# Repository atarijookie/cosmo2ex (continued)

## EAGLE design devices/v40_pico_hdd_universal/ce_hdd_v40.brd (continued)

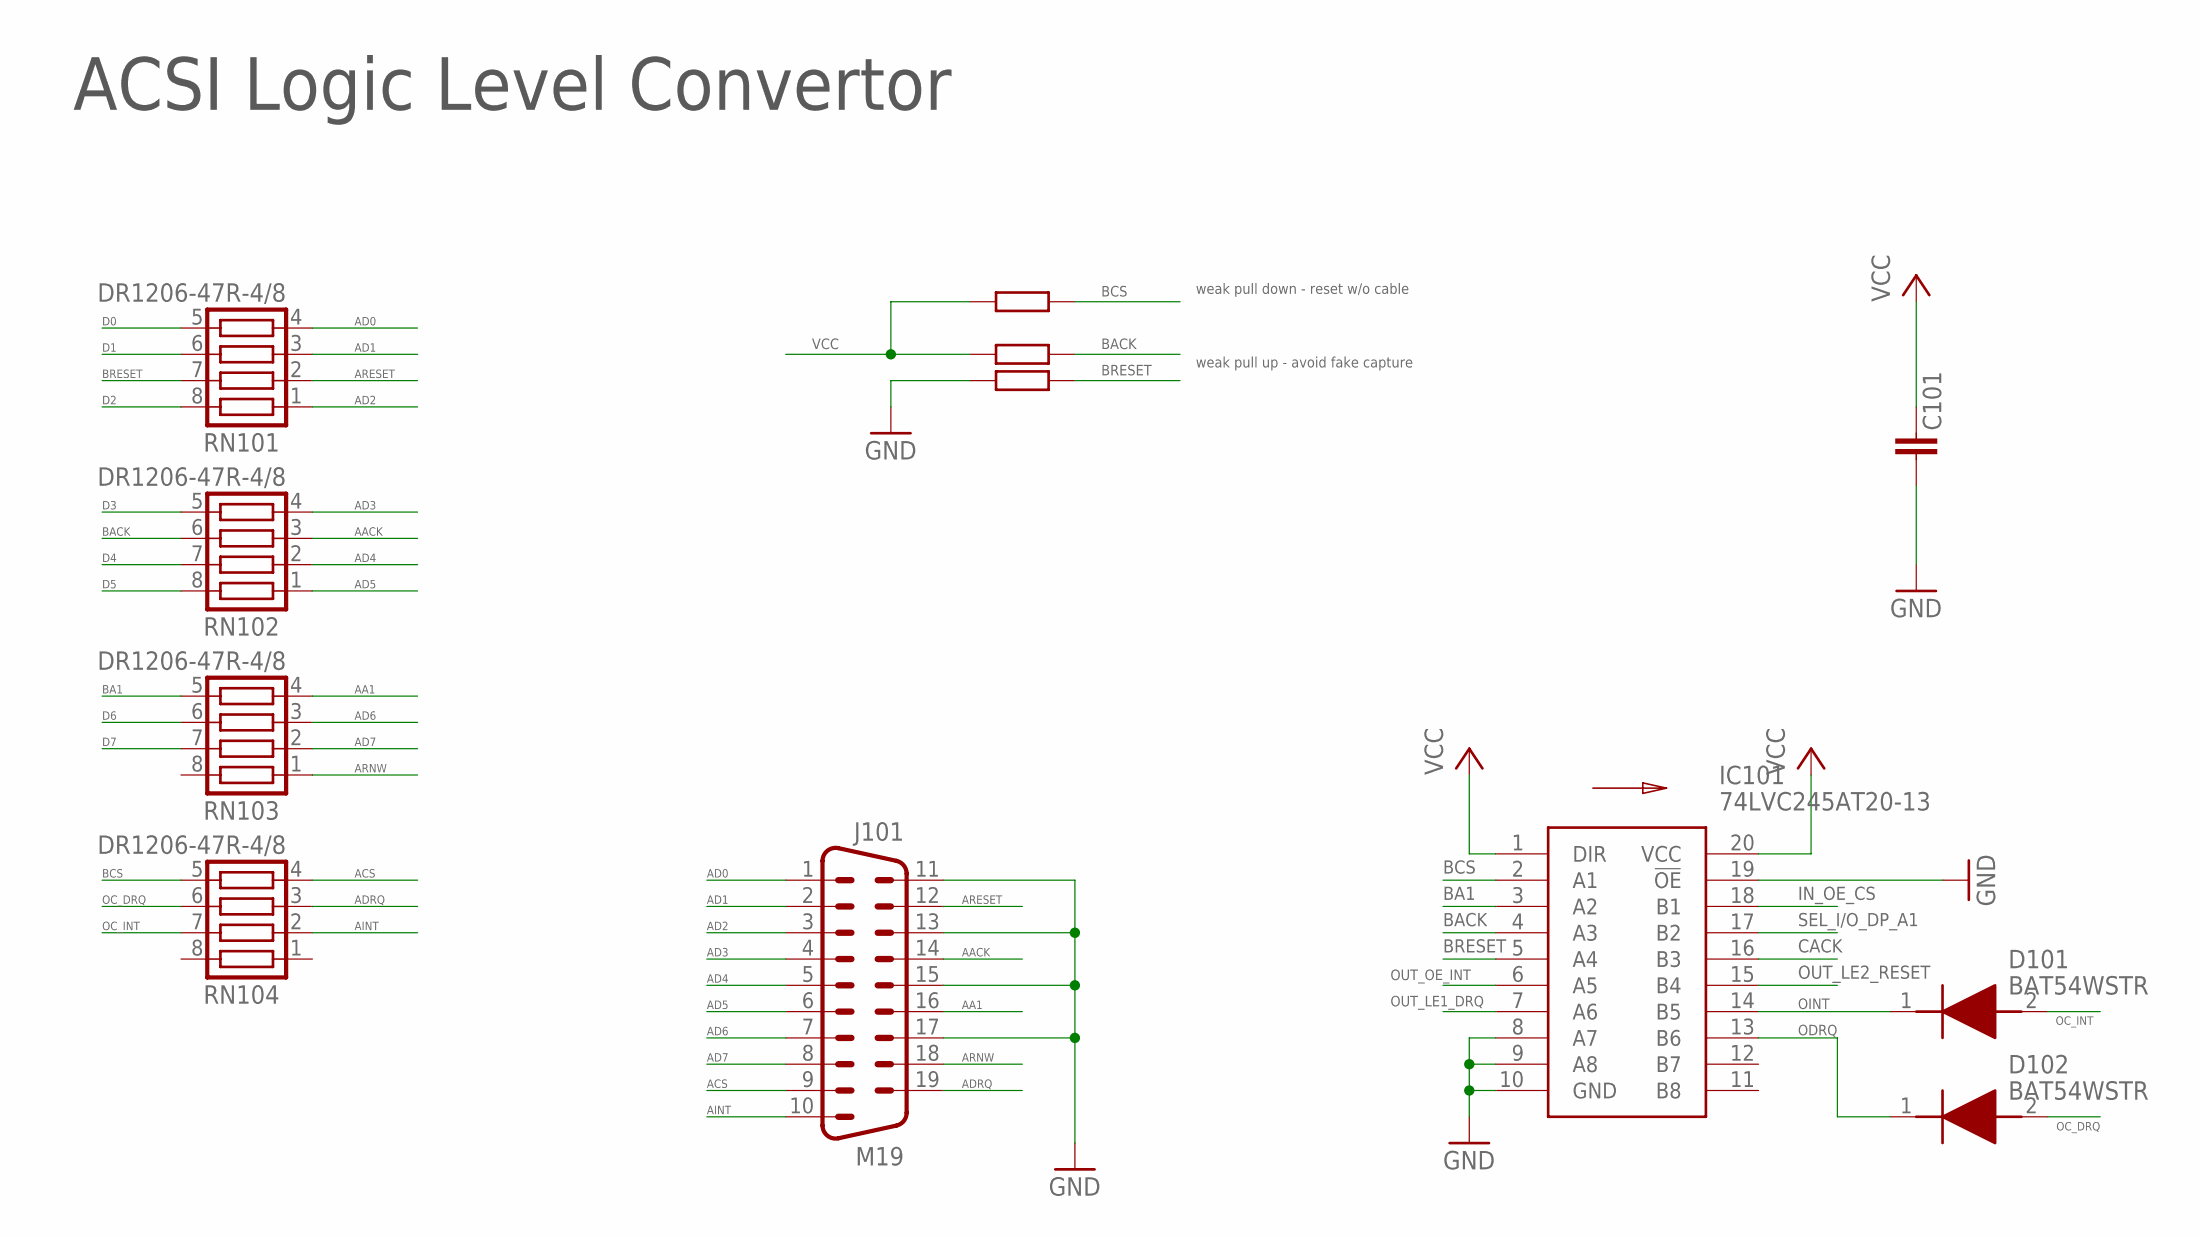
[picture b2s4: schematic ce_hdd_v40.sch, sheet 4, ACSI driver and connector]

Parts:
C101: 1 uF; C0603
D101: BAT54WSTR; SOD2613X100N
D102: BAT54WSTR; SOD2613X100N; MANUFACTURER_PART_NUMBER BAT54WSTR
IC101: 74LVC245AT20-13; SOP65P640X120-20N
J101: M19
R102, R103, R104: 10k; R0603
RN101, RN102, RN103, RN104: DR1206-47R-4/8; CTS742C083

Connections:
AA1: J101.16, RN103.4
AACK: J101.14, RN102.3
ACS: J101.9, RN104.4
AD0: J101.1, RN101.4
AD1: J101.2, RN101.3
AD2: J101.3, RN101.1
AD3: J101.4, RN102.4
AD4: J101.5, RN102.2
AD5: J101.6, RN102.1
AD6: J101.7, RN103.3
AD7: J101.8, RN103.2
ADRQ: J101.19, RN104.3
AINT: J101.10, RN104.2
ARESET: J101.12, RN101.2
ARNW: J101.18, RN103.1
BA1: IC101.3 (A2), RN103.5
BACK: IC101.4 (A3), R103.2, RN102.6
BCS: IC101.2 (A1), R102.2, RN104.5
BRESET: IC101.5 (A4), R104.2, RN101.7
CACK: IC101.16 (B3); also elsewhere on the board
D0: RN101.5; also elsewhere on the board
D1: RN101.6; also elsewhere on the board
D2: RN101.8; also elsewhere on the board
D3: RN102.5; also elsewhere on the board
D4: RN102.7; also elsewhere on the board
D5: RN102.8; also elsewhere on the board
D6: RN103.6; also elsewhere on the board
D7: RN103.7; also elsewhere on the board
GND: C101.2, IC101.8 (A7), IC101.9 (A8), IC101.10 (GND), IC101.19 (!OE), J101.11, J101.13, J101.15, J101.17, R104.1; also elsewhere on the board
IN_OE_CS: IC101.18 (B1); also elsewhere on the board
OC_DRQ: D102.2 (A), RN104.6
OC_INT: D101.2 (A), RN104.7
ODRQ: D102.1 (K), IC101.13 (B6)
OINT: D101.1 (K), IC101.14 (B5)
OUT_LE1_DRQ: IC101.7 (A6); also elsewhere on the board
OUT_LE2_RESET: IC101.15 (B4); also elsewhere on the board
OUT_OE_INT: IC101.6 (A5); also elsewhere on the board
SEL_I/O_DP_A1: IC101.17 (B2); also elsewhere on the board
VCC: C101.1, IC101.1 (DIR), IC101.20 (VCC), R102.1, R103.1; also elsewhere on the board

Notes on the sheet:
ACSI Logic Level Convertor
weak pull down - reset w/o cable
weak pull up - avoid fake capture

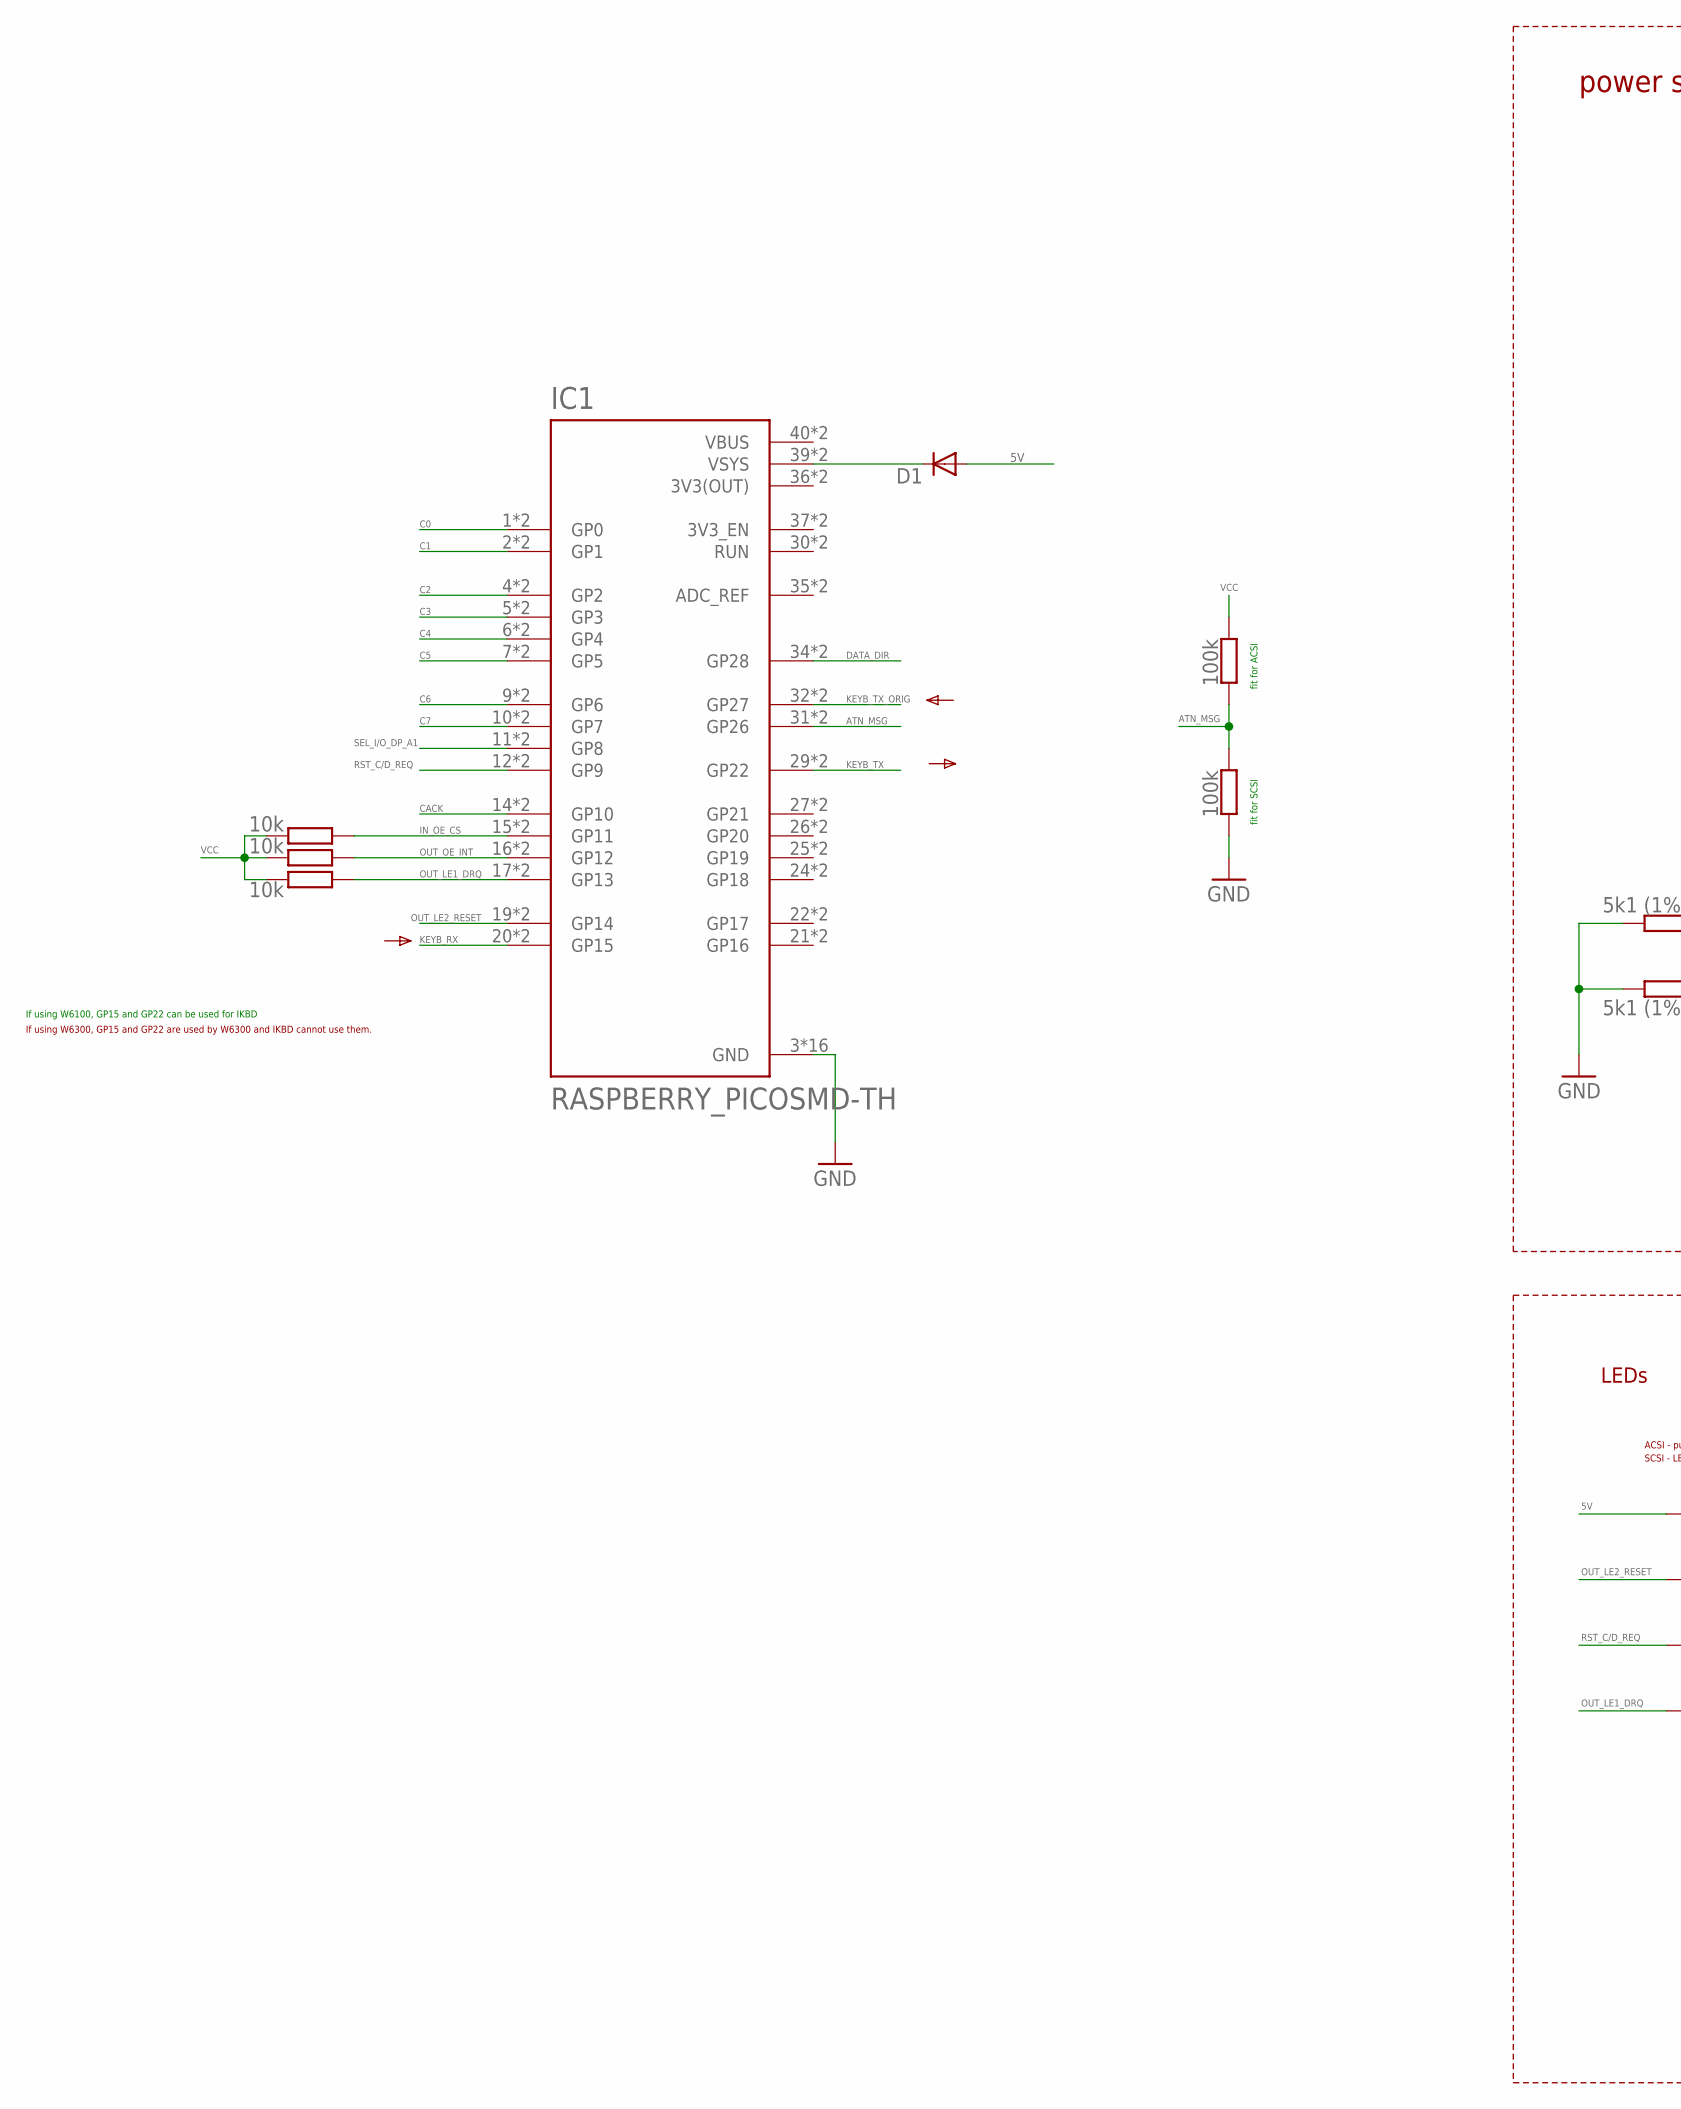
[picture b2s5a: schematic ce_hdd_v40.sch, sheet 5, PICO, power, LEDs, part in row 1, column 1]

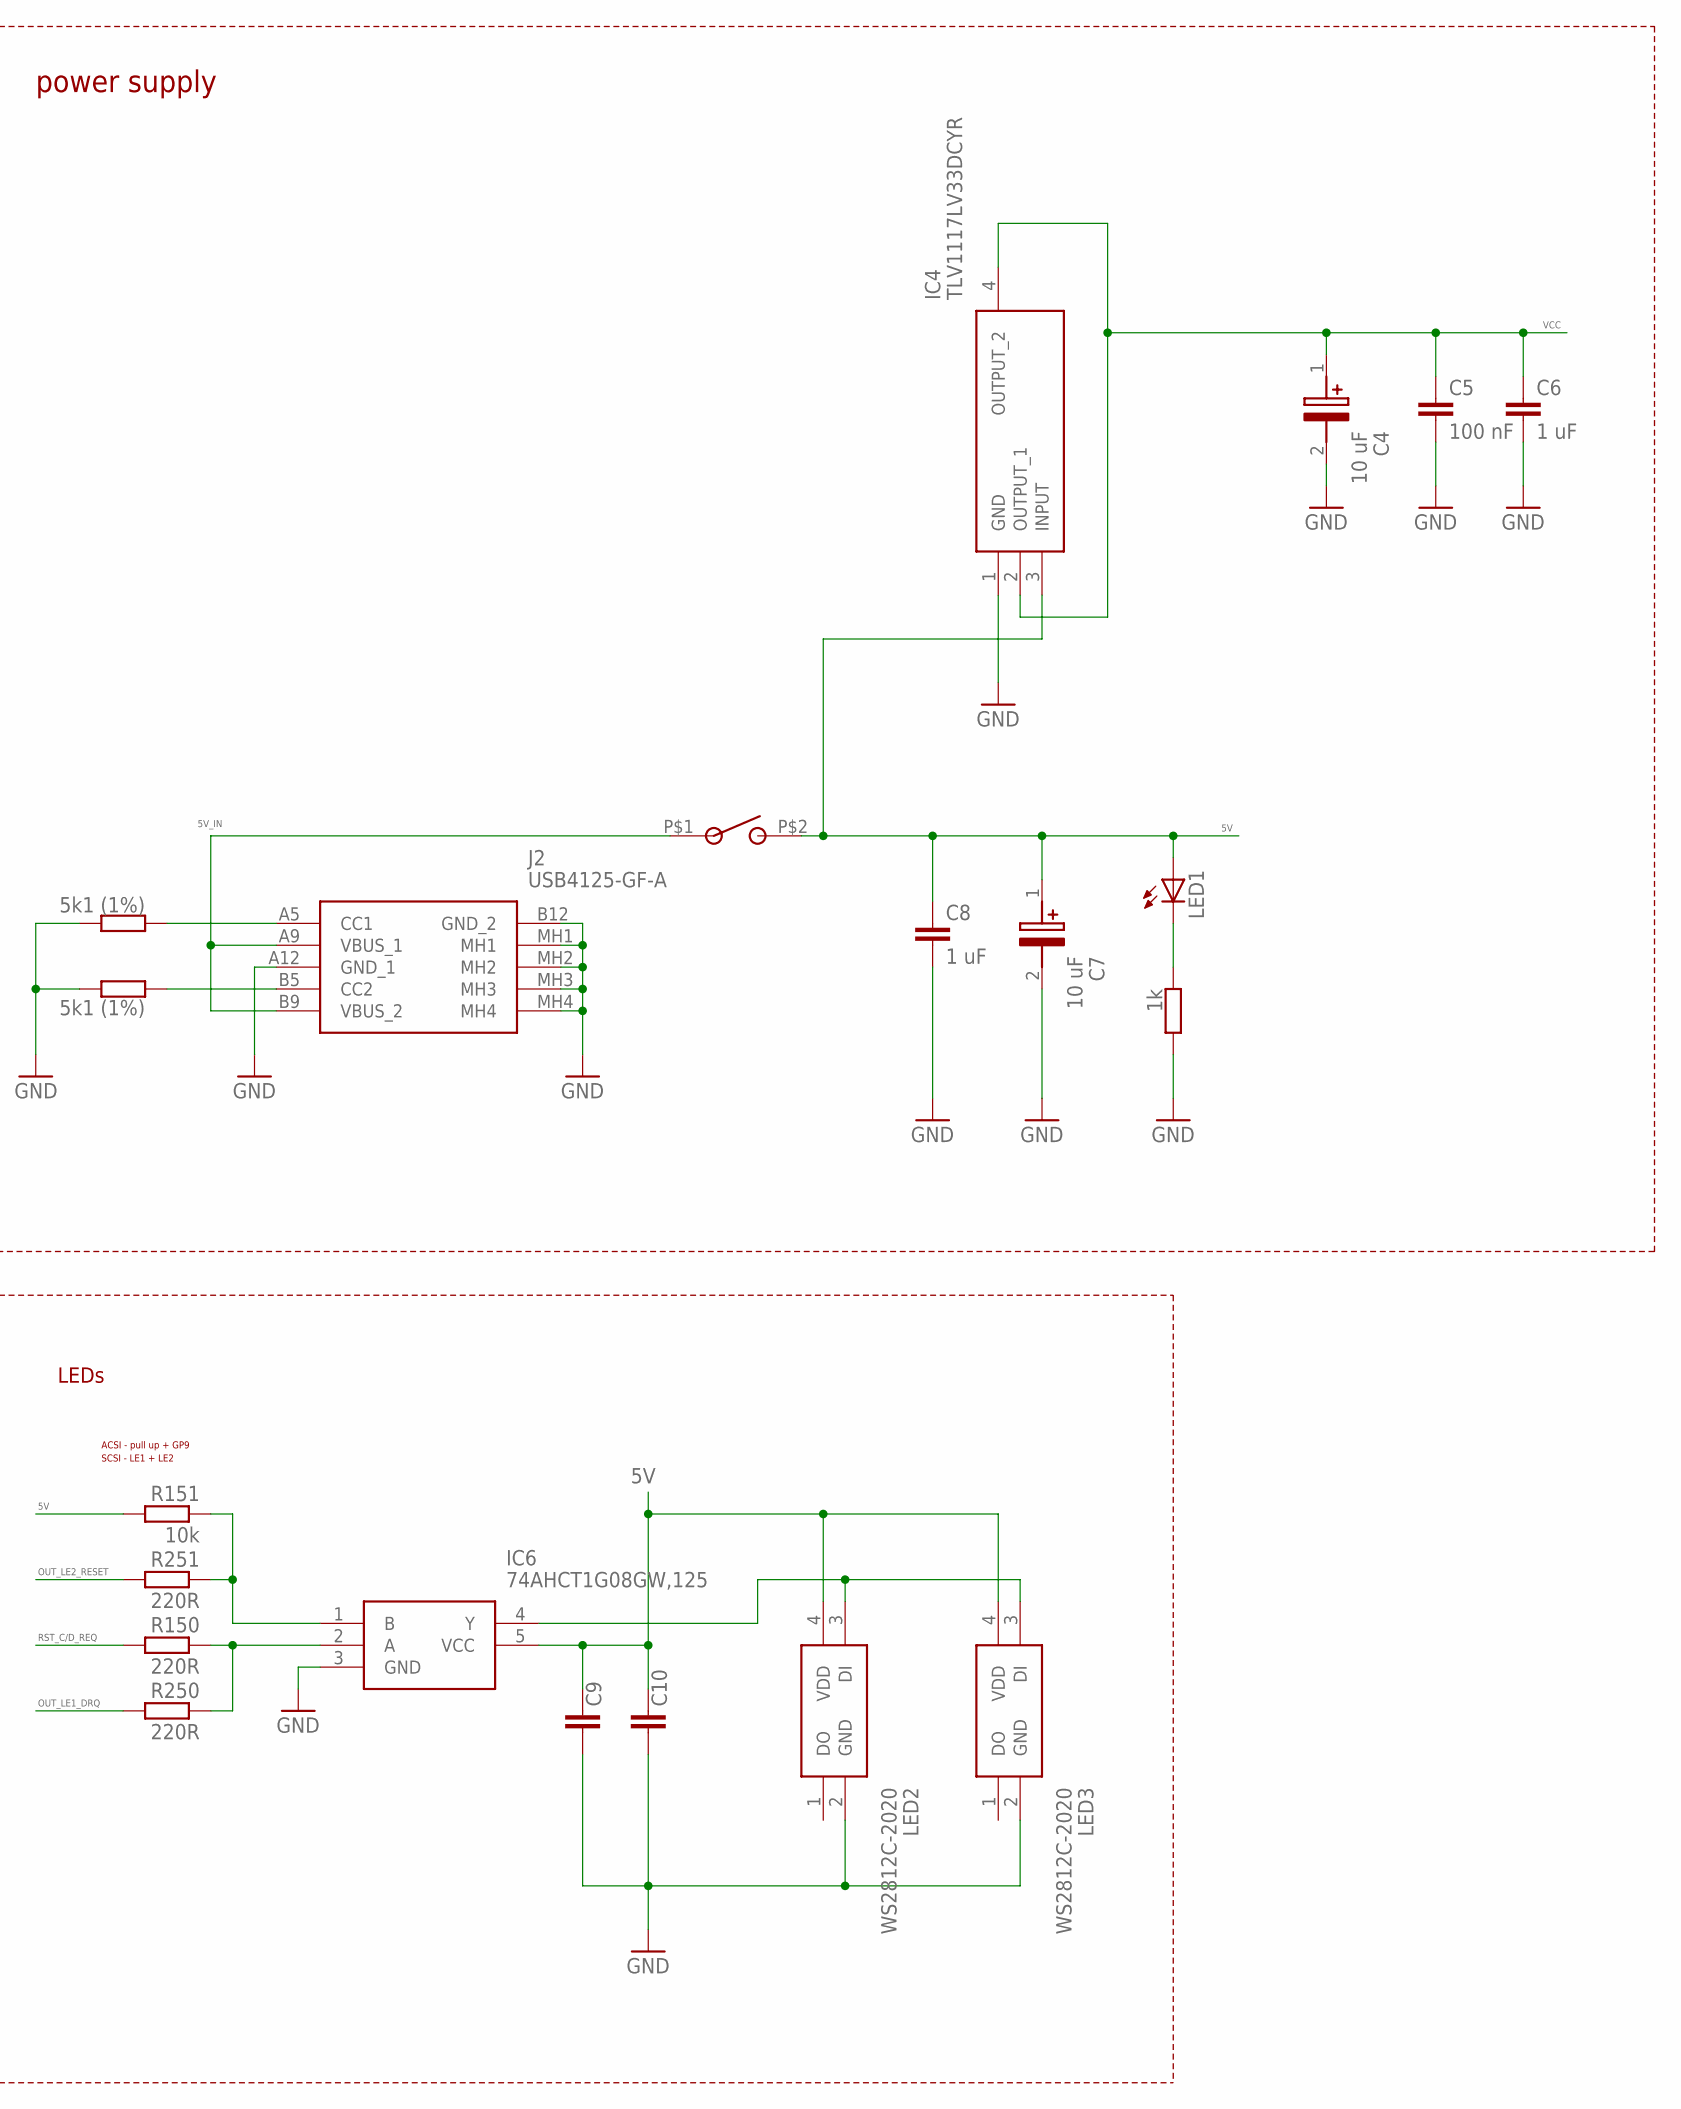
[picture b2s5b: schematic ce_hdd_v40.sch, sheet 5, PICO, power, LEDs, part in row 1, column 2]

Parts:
C4: 10 uF; CAPPM3528X210N; MANUFACTURER_PART_NUMBER 293D106X9016B2TE3
C5, C9, C10: 100 nF; C0603
C6, C8: 1 uF; C0603
C7: 10 uF; CAPPM3528X210N
D1: SK110-DIO; DO214AC
IC1: RASPBERRY_PICOSMD-TH; PICO-PKG
IC4: TLV1117LV33DCYR; SOT230P700X180-4N
IC6: 74AHCT1G08GW,125; SOT65P212X110-5N
J2: USB4125-GF-A; USB4125GFA
LED1: LEDSML0603; SML0603
LED2: WS2812C-2020; WS2812C2020
LED3: WS2812C-2020; WS2812C2020; MANUFACTURER_PART_NUMBER WS2812C-2020
R3, R4: 5k1 (1%); R0603
R5: 1k; R0603
R6, R7, R8, R151: 10k; R0603
R125, R225: 100k; R0603
R150, R250, R251: 220R; R0603
SW1: SMSR-1; SMRS-1

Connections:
3V3(OUT): IC1.36 (3V3(OUT)), IC1.P$36 (3V3(OUT))
5V: C7.1 (+), C8.1, C9.1, C10.1, D1.A, IC4.3 (INPUT), IC6.5 (VCC), LED1.A, LED2.4 (VDD), LED3.4 (VDD), R151.2, SW1.P$2; also elsewhere on the board
5V_IN: J2.A9 (VBUS_1), J2.B9 (VBUS_2), SW1.P$1
ATN_MSG: IC1.31 (GP26), IC1.P$31 (GP26), R125.2, R225.1; also elsewhere on the board
C0: IC1.1 (GP0), IC1.P$1 (GP0); also elsewhere on the board
C1: IC1.2 (GP1), IC1.P$2 (GP1); also elsewhere on the board
C2: IC1.4 (GP2), IC1.P$4 (GP2); also elsewhere on the board
C3: IC1.5 (GP3), IC1.P$5 (GP3); also elsewhere on the board
C4: IC1.6 (GP4), IC1.P$6 (GP4); also elsewhere on the board
C5: IC1.7 (GP5), IC1.P$7 (GP5); also elsewhere on the board
C6: IC1.9 (GP6), IC1.P$9 (GP6); also elsewhere on the board
C7: IC1.10 (GP7), IC1.P$10 (GP7); also elsewhere on the board
CACK: IC1.14 (GP10), IC1.P$14 (GP10); also elsewhere on the board
DATA_DIR: IC1.34 (GP28), IC1.P$34 (GP28); also elsewhere on the board
GND: C4.2 (-), C5.2, C6.2, C7.2 (-), C8.2, C9.2, C10.2, IC1.3 (GND), IC1.8 (GND), IC1.13 (GND), IC1.18 (GND), IC1.23 (GND), IC1.28 (GND), IC1.33 (GND), IC1.38 (GND), IC1.P$3 (GND), IC1.P$8 (GND), IC1.P$13 (GND), IC1.P$18 (GND), IC1.P$23 (GND), IC1.P$28 (GND), IC1.P$33 (GND), IC1.P$38 (GND), IC4.1 (GND), IC6.3 (GND), J2.A12 (GND_1), J2.B12 (GND_2), J2.MH1, J2.MH2, J2.MH3, J2.MH4, LED2.2 (GND), LED3.2 (GND), R3.2, R4.2, R5.2, R225.2; also elsewhere on the board
IN_OE_CS: IC1.15 (GP11), IC1.P$15 (GP11), R6.2; also elsewhere on the board
KEYB_RX: IC1.20 (GP15), IC1.P$20 (GP15); also elsewhere on the board
KEYB_TX: IC1.29 (GP22), IC1.P$29 (GP22); also elsewhere on the board
KEYB_TX_ORIG: IC1.32 (GP27), IC1.P$32 (GP27); also elsewhere on the board
unnamed: J2.B5 (CC2), R4.1
unnamed: J2.A5 (CC1), R3.1
unnamed: IC6.2 (A), R150.1, R250.1
unnamed: IC6.1 (B), R151.1, R251.1
unnamed: LED1.C, R5.1
unnamed: IC6.4 (Y), LED2.3 (DI), LED3.3 (DI)
unnamed: D1.C, IC1.39 (VSYS), IC1.P$39 (VSYS)
OUT_LE1_DRQ: IC1.17 (GP13), IC1.P$17 (GP13), R8.2, R250.2; also elsewhere on the board
OUT_LE2_RESET: IC1.19 (GP14), IC1.P$19 (GP14), R251.2; also elsewhere on the board
OUT_OE_INT: IC1.16 (GP12), IC1.P$16 (GP12), R7.2; also elsewhere on the board
RST_C/D_REQ: IC1.12 (GP9), IC1.P$12 (GP9), R150.2; also elsewhere on the board
SEL_I/O_DP_A1: IC1.11 (GP8), IC1.P$11 (GP8); also elsewhere on the board
VBUS: IC1.40 (VBUS), IC1.P$40 (VBUS)
VCC: C4.1 (+), C5.1, C6.1, IC4.2 (OUTPUT_1), IC4.4 (OUTPUT_2), R6.1, R7.1, R8.1, R125.1; also elsewhere on the board

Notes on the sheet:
power supply
If using W6100, GP15 and GP22 can be used for IKBD
If using W6300, GP15 and GP22 are used by W6300 and IKBD cannot use them.
fit for ACSI
fit for SCSI
LEDs
ACSI - pull up + GP9
SCSI - LE1 + LE2

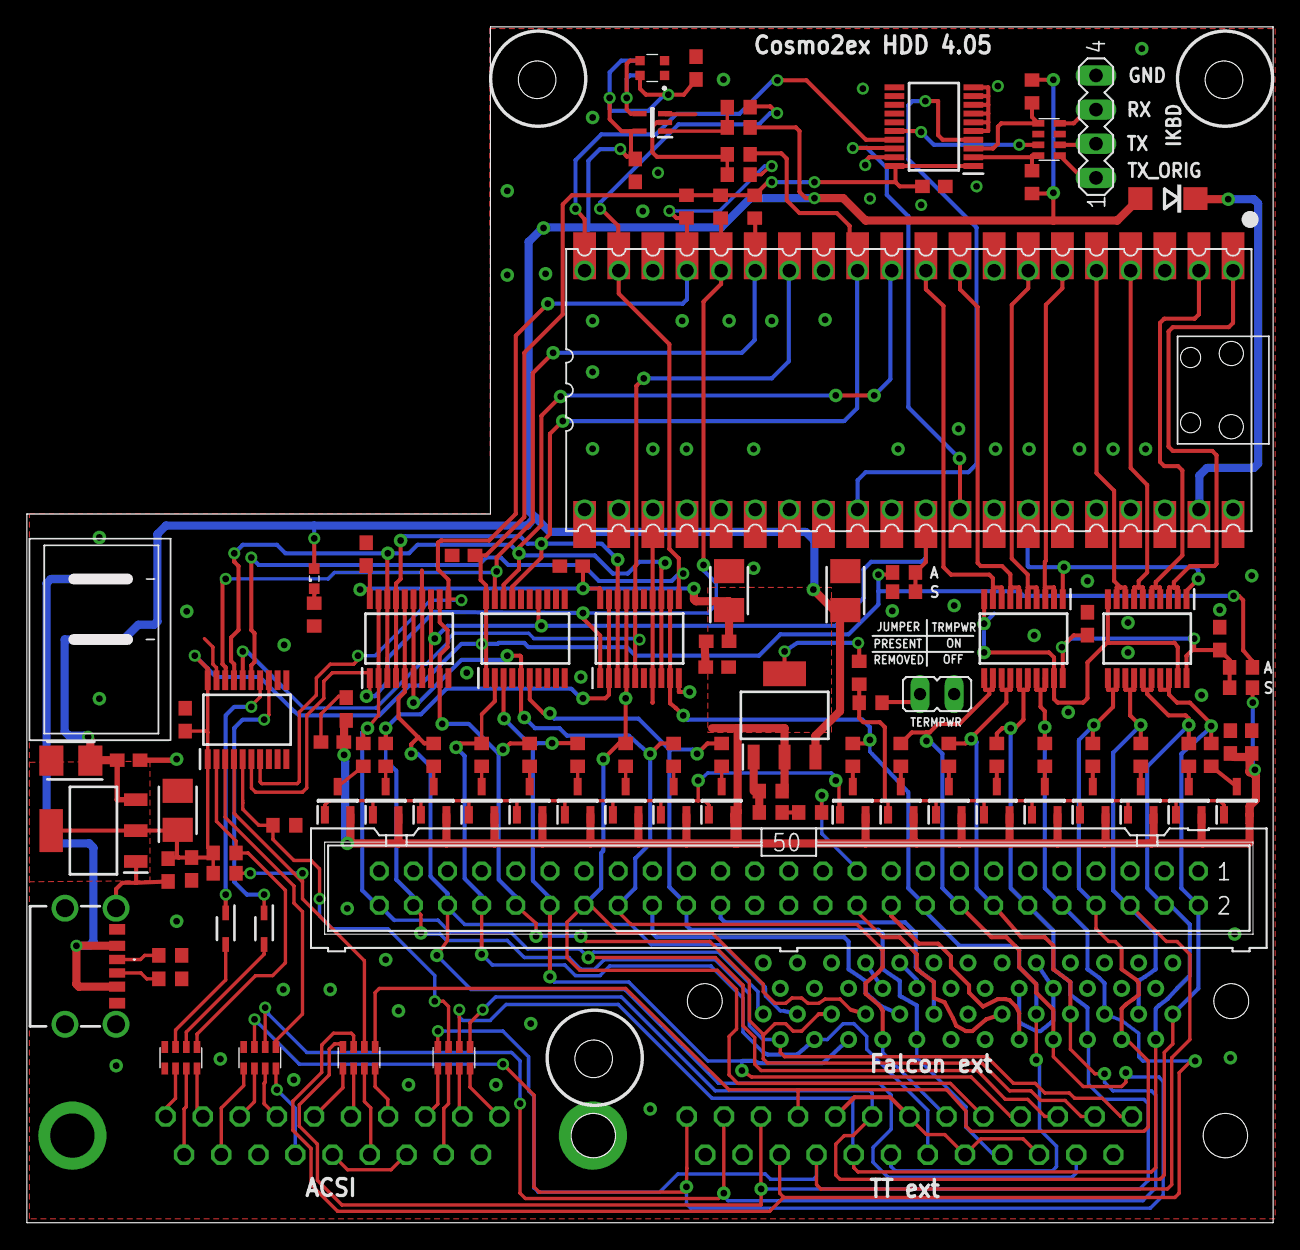
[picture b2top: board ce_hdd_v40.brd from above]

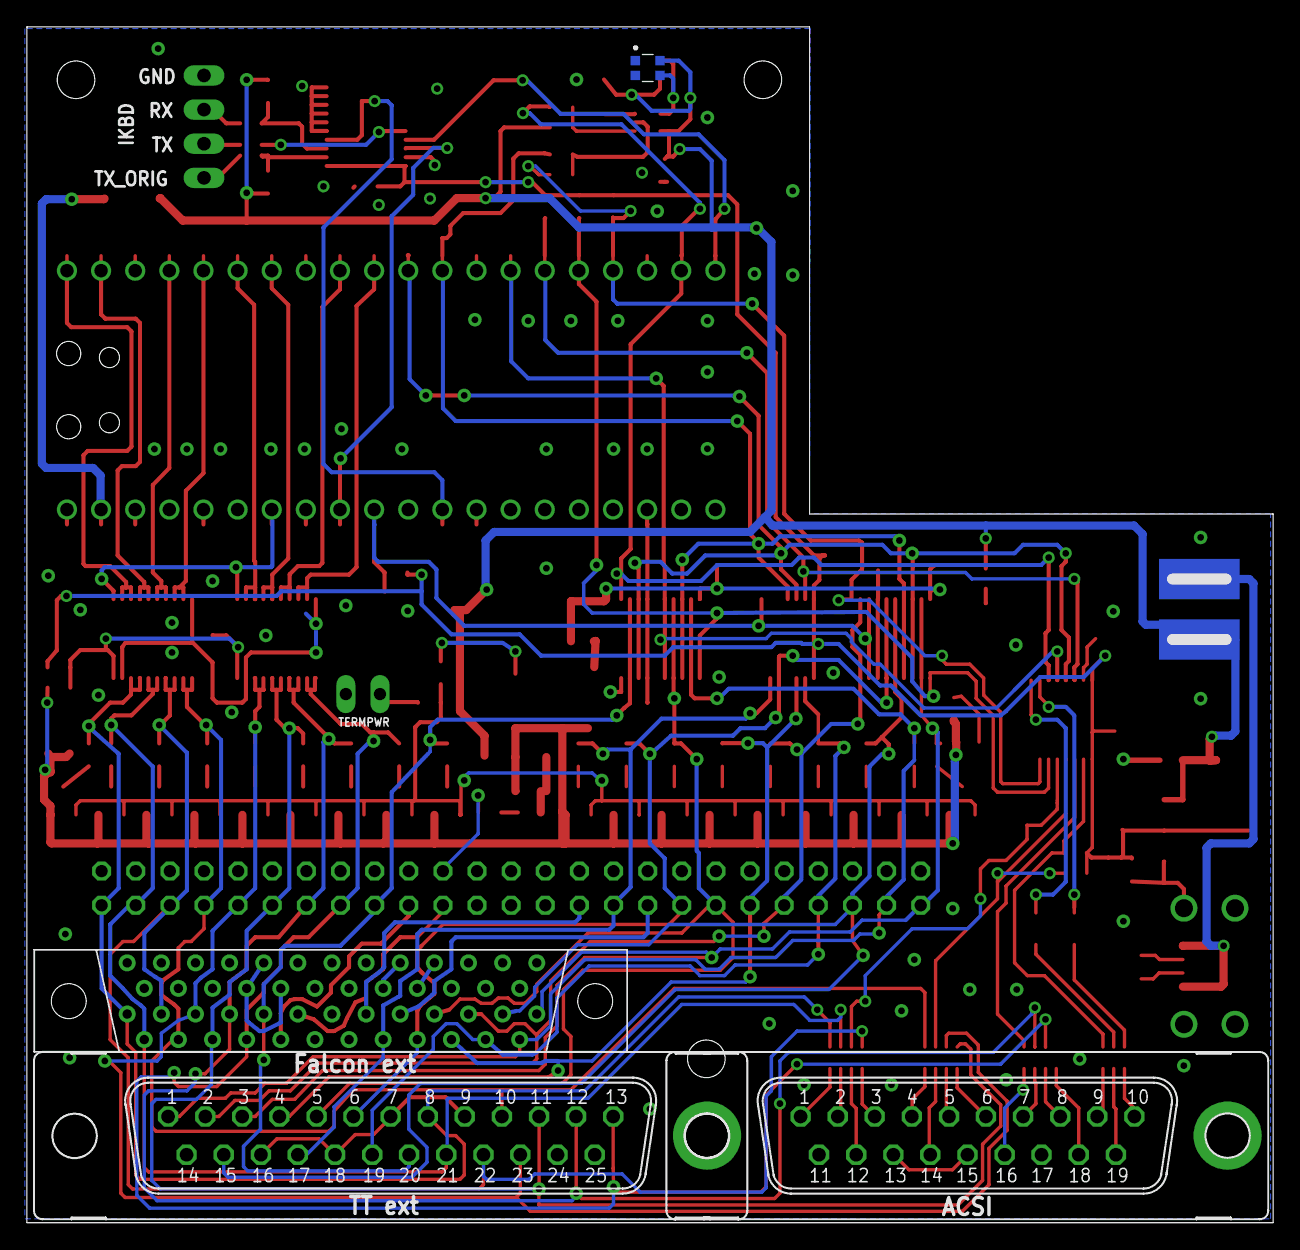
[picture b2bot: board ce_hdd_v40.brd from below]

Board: 2 copper layers, 92.8 x 89.0 mm, 112 parts (4 on the bottom side), 104 nets.

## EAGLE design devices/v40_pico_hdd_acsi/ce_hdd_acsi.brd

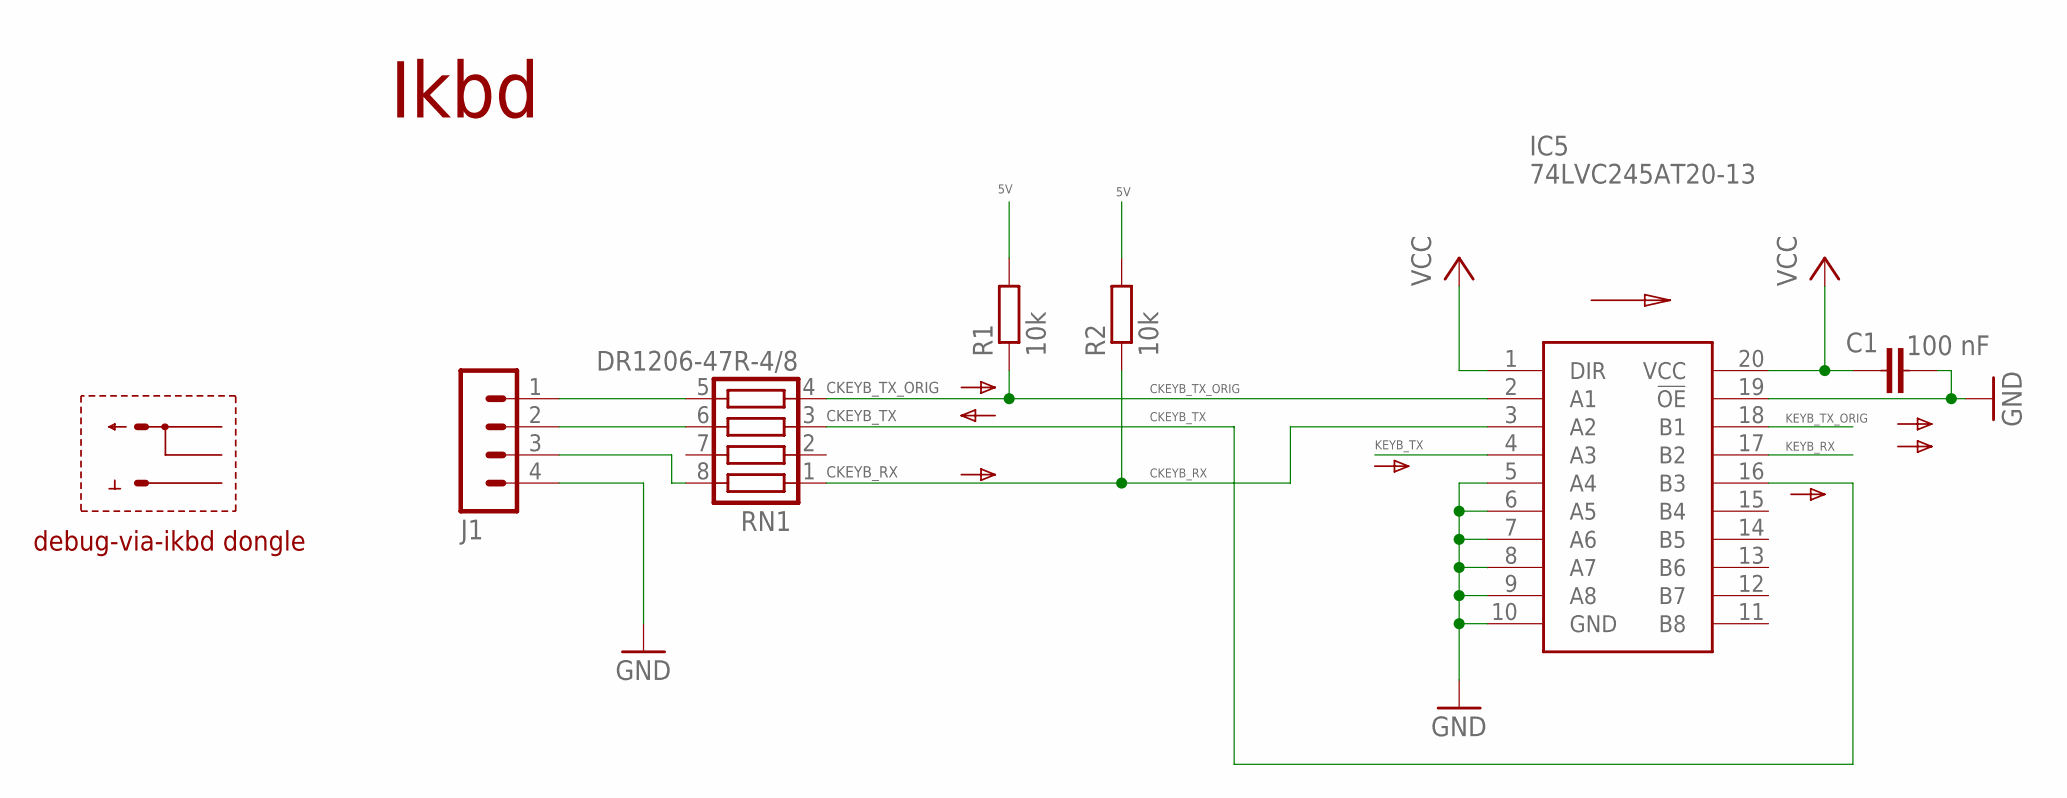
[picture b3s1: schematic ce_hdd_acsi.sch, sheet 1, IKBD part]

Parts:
C1: 100 nF; C0603
IC5: 74LVC245AT20-13; SOP65P640X120-20N
J1: MA04-1
R1, R2: 10k; R0603
RN1: DR1206-47R-4/8; CTS742C083

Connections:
5V: R1.2, R2.2; also elsewhere on the board
CKEYB_RX: IC5.3 (A2), R2.1, RN1.1
CKEYB_TX: IC5.16 (B3), RN1.3
CKEYB_TX_ORIG: IC5.2 (A1), R1.1, RN1.4
GND: C1.1, IC5.5 (A4), IC5.6 (A5), IC5.7 (A6), IC5.8 (A7), IC5.9 (A8), IC5.10 (GND), IC5.19 (!OE), J1.4; also elsewhere on the board
KEYB_RX: IC5.17 (B2); also elsewhere on the board
KEYB_TX: IC5.4 (A3); also elsewhere on the board
KEYB_TX_ORIG: IC5.18 (B1); also elsewhere on the board
unnamed: J1.2, RN1.6
VCC: C1.2, IC5.1 (DIR), IC5.20 (VCC); also elsewhere on the board
ZKEYB_RX: J1.3, RN1.8
ZKEYB_TX_ORIG: J1.1, RN1.5

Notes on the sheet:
Ikbd
debug-via-ikbd dongle
